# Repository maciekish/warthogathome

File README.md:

# Warthog at Home

This is a compilation of various resources to build an A-10C II cockpit for home entertainment. It is loosely based on [The Warthog Project](http://thewarthogproject.com) and frame designs by Flim on the ED forums.

This project started out as an idea for 3d-printed panels for the F-GT Lite racing chair, but as time went on it became more and more obvious that it's just too small and i would have to make way too many compromises along the way. For this reason i decided to use some of the available resources online to build a proper cockpit, but still trying to keep it as "stowable" as possible by making it modular and not mounted to the floor.

## License

This project is licensed under the MIT License except as stated otherwise in certain parts not made by me.

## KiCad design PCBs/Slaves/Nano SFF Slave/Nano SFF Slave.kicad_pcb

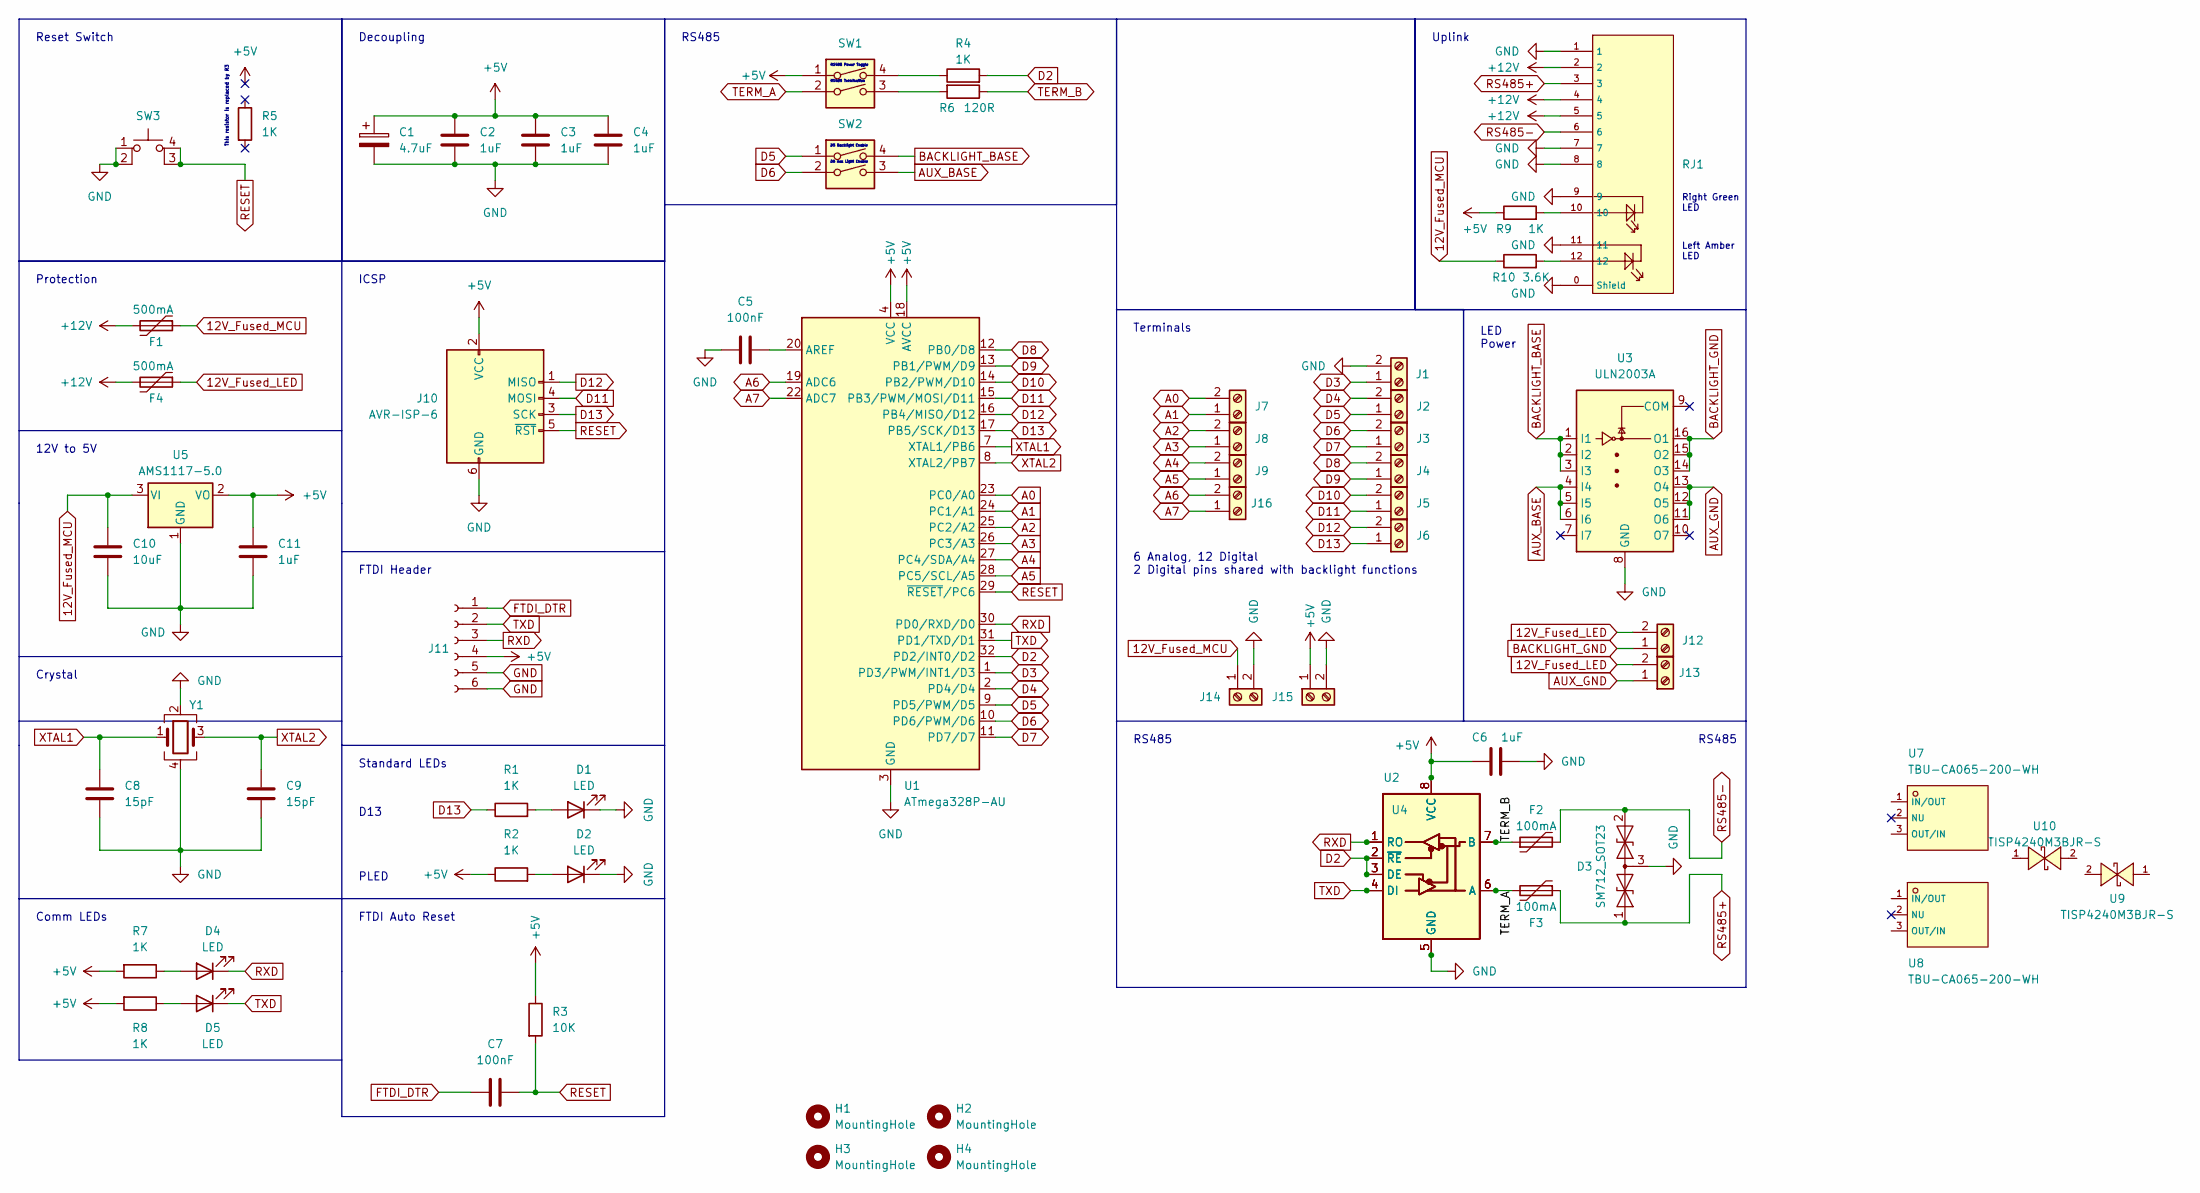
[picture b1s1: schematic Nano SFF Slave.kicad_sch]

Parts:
C1: 4.7uF; C0805; LCSC C1779
C2, C3, C4, C6, C11: 1uF; C0402; LCSC C52923
C5, C7: 100nF; C0402; LCSC C1525
C8, C9: 15pF; C0402; LCSC C1548
C10: 10uF; C0402; LCSC C15525
D1, D2, D4, D5: LED; LED_0603_1608Metric; LCSC C72041
D3: SM712_SOT23; SOT-23; LCSC C558433
F1, F4: 500mA; Fuse_1206_3216Metric; LCSC C369159
F2, F3: 100mA; Fuse_0603_1608Metric; LCSC C207238
H1, H2, H3, H4: MountingHole; MountingHole_3.2mm_M3
J1, J2, J3, J4, J5, J6, J7, J8, J9, J12, J13, J14, J15, J16: Screw_Terminal_01x02; CONN-TH_XY308-2.54-2P; LCSC C557685
J10: AVR-ISP-6; PinHeader_2x03_P2.54mm_Vertical; LCSC C492420
J11: Conn_01x06_Female; PinSocket_1x06_P2.54mm_Vertical; LCSC C40877
R1, R2, R4, R7, R8, R9: 1K; R_0402_1005Metric; LCSC C11702
R3: 10K; R_0805_2012Metric; LCSC C17414
R5: 1K; R_0805_2012Metric; LCSC C17513
R6: 120R; R_0805_2012Metric; LCSC C17437
R10: 3.6K; R_0603_1608Metric; LCSC C22980
RJ1: RJ45-B-1*1; RJ45-TH_B-1-1; LCSC C138392
SW1, SW2: SW_DIP_x02; SW-SMD_DSHP02TSGER; LCSC C367376
SW3: SW_MEC_5E; SW-SMD_4P-L5.1-W5.1-P3.70-LS6.5-TL-2; LCSC C318884
U1: ATmega328P-AU; TQFP-32_7x7mm_P0.8mm; LCSC C14877
U2: MAX487ESA+T; SOIC-8_L5.0-W4.0-P1.27-LS6.0-BL; LCSC C9953
U3: ULN2003A; SOP-16_L10.0-W3.9-P1.27-LS6.0-BL; LCSC C7512
U4: MAX487CPA+; DIP-8_W7.62mm
U5: AMS1117-5.0; SOT-223-3_TabPin2; LCSC C6187
U7, U8: TBU-CA065-200-WH; DIO-SMD_3P-L6.5-W4.0-BI; LCSC C913221
U9, U10: TISP4240M3BJR-S; DO-214AA_L4.4-W3.6-LS5.3-BI; LCSC C840526
Y1: Crystal_GND24; Crystal_SMD_3225-4Pin_3.2x2.5mm; LCSC C13738

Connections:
12V_Fused_LED: F4.1, J12.2, J13.2
12V_Fused_MCU: C10.1, F1.1, J14.1, R10.1, U5.3 (VI)
+5V: C1.1, C2.1, C3.1, C4.1, C6.1, C11.1, J10.2 (VCC), J11.4, J15.1, R2.1, R3.1, R7.2, R8.2, R9.1, SW1.1, U1.4 (VCC), U1.6 (VCC), U1.18 (AVCC), U2.8 (VCC), U4.8 (VCC), U5.2 (VO)
+12V: F1.2, F4.2, RJ1.2, RJ1.4, RJ1.5
A0: J7.2, U1.23 (PC0/A0)
A1: J7.1, U1.24 (PC1/A1)
A2: J8.2, U1.25 (PC2/A2)
A3: J8.1, U1.26 (PC3/A3)
A4: J9.2, U1.27 (PC4/SDA/A4)
A5: J9.1, U1.28 (PC5/SCL/A5)
A6: J16.2, U1.19 (ADC6)
A7: J16.1, U1.22 (ADC7)
AUX_BASE: SW2.3, U3.4 (I4), U3.5 (I5), U3.6 (I6)
AUX_GND: J13.1, U3.11 (O6), U3.12 (O5), U3.13 (O4)
BACKLIGHT_BASE: SW2.4, U3.1 (I1), U3.2 (I2), U3.3 (I3)
BACKLIGHT_GND: J12.1, U3.14 (O3), U3.15 (O2), U3.16 (O1)
D2: R4.2, U1.32 (PD2/INT0/D2), U2.2 (~RE), U2.3 (DE), U4.2 (~RE), U4.3 (DE)
D3: J1.1, U1.1 (PD3/PWM/INT1/D3)
D4: J2.2, U1.2 (PD4/D4)
D5: J2.1, SW2.1, U1.9 (PD5/PWM/D5)
D6: J3.2, SW2.2, U1.10 (PD6/PWM/D6)
D7: J3.1, U1.11 (PD7/D7)
D8: J4.2, U1.12 (PB0/D8)
D9: J4.1, U1.13 (PB1/PWM/D9)
D10: J5.2, U1.14 (PB2/PWM/D10)
D11: J5.1, J10.4 (MOSI), U1.15 (PB3/PWM/MOSI/D11)
D12: J6.2, J10.1 (MISO), U1.16 (PB4/MISO/D12)
D13: J6.1, J10.3 (SCK), R1.1, U1.17 (PB5/SCK/D13)
FTDI_DTR: C7.2, J11.1
GND: C1.2, C2.2, C3.2, C4.2, C5.1, C6.2, C8.1, C9.2, C10.2, C11.2, D1.1 (K), D2.1 (K), D3.3 (common), J1.2, J10.6 (GND), J11.5, J11.6, J14.2, J15.2, RJ1.0 (Shield), RJ1.1, RJ1.7, RJ1.8, RJ1.9, RJ1.11, SW3.1, SW3.2, U1.3 (GND), U1.5 (GND), U1.21 (GND), U2.5 (GND), U3.8 (GND), U4.5 (GND), U5.1 (GND), Y1.2, Y1.4
unnamed: C5.2, U1.20 (AREF)
unnamed: D1.2 (A), R1.2
unnamed: D2.2 (A), R2.2
unnamed: D4.2 (A), R7.1
unnamed: D5.2 (A), R8.1
unnamed: R4.1, SW1.4
unnamed: R6.2, SW1.3
unnamed: R9.2, RJ1.10
unnamed: R10.2, RJ1.12
RESET: C7.1, J10.5 (~RST), R3.2, SW3.3 (K), SW3.4 (A), U1.29 (~RESET/PC6)
RS485+: D3.1 (A1), F3.1, RJ1.3
RS485-: D3.2 (A2), F2.2, RJ1.6
RXD: D4.1 (K), J11.3, U1.30 (PD0/RXD/D0), U2.1 (RO), U4.1 (RO)
TERM_A: F3.2, SW1.2, U2.6 (A), U4.6 (A)
TERM_B: F2.1, R6.1, U2.7 (B), U4.7 (B)
TXD: D5.1 (K), J11.2, U1.31 (PD1/TXD/D1), U2.4 (DI), U4.4 (DI)
XTAL1: C8.2, U1.7 (XTAL1/PB6), Y1.1
XTAL2: C9.1, U1.8 (XTAL2/PB7), Y1.3

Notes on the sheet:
RS485
Comm LEDs
Decoupling
Left Amber LED
D13
12V to 5V
Uplink
D5 Backlight Enable
RS485 Power Toggle
Protection
6 Analog, 12 Digital 2 Digital pins shared with backlight functions
Terminals
RS485 Termination
PLED
FTDI Header
D6 Aux Light Enable
Standard LEDs
LED Power
Right Green LED
FTDI Auto Reset
Reset Switch
Crystal
ICSP
This resistor is replaced by R3

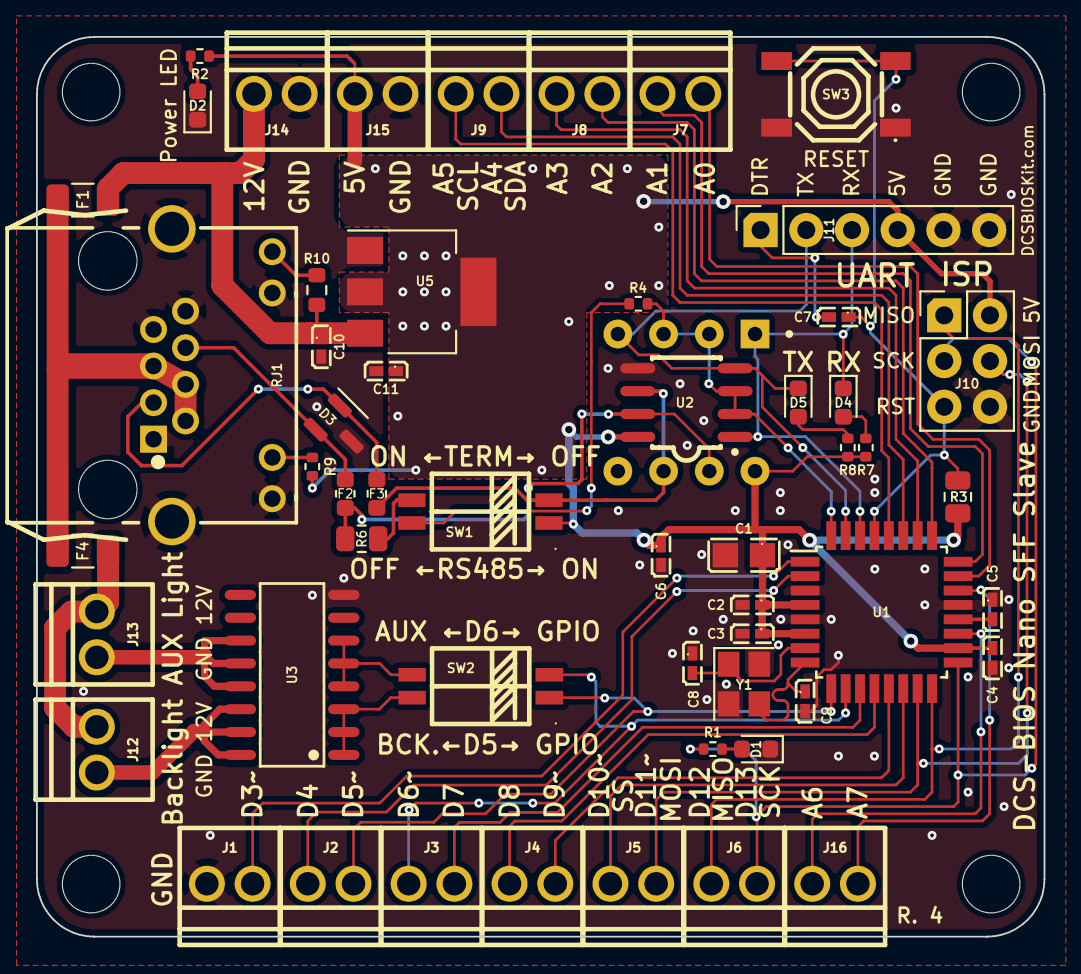
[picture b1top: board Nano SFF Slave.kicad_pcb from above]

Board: 2 copper layers, 56.0 x 50.0 mm, 59 parts (0 on the bottom side), 48 nets.

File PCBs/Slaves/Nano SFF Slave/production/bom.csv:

Designator,Footprint,Quantity,Value,LCSC Part #
J3,CONN-TH_XY308-2.54-2P,1,Screw_Terminal_01x02,C557685
R4,R_0402_1005Metric,1,1K,C11702
J10,PinHeader_2x03_P2.54mm_Vertical,1,AVR-ISP-6,C492420
J5,CONN-TH_XY308-2.54-2P,1,Screw_Terminal_01x02,C557685
F4,Fuse_1206_3216Metric,1,500mA,C369159
H4,MountingHole_3.2mm_M3,1,MountingHole,
R2,R_0402_1005Metric,1,1K,C11702
C6,C0402,1,1uF,C52923
U5,SOT-223-3_TabPin2,1,AMS1117-5.0,C6187
F1,Fuse_1206_3216Metric,1,500mA,C369159
H3,MountingHole_3.2mm_M3,1,MountingHole,
R7,R_0402_1005Metric,1,1K,C11702
D5,LED_0603_1608Metric,1,LED,C72041
C3,C0402,1,1uF,C52923
J15,CONN-TH_XY308-2.54-2P,1,Screw_Terminal_01x02,C557685
C1,C0805,1,4.7uF,C1779
C5,C0402,1,100nF,C1525
U3,SOP-16_L10.0-W3.9-P1.27-LS6.0-BL,1,ULN2003A,C7512
C11,C0402,1,1uF,C52923
C2,C0402,1,1uF,C52923
U2,SOIC-8_L5.0-W4.0-P1.27-LS6.0-BL,1,MAX487ESA+T,C9953
J14,CONN-TH_XY308-2.54-2P,1,Screw_Terminal_01x02,C557685
D2,LED_0603_1608Metric,1,LED,C72041
R8,R_0402_1005Metric,1,1K,C11702
H1,MountingHole_3.2mm_M3,1,MountingHole,
J1,CONN-TH_XY308-2.54-2P,1,Screw_Terminal_01x02,C557685
J6,CONN-TH_XY308-2.54-2P,1,Screw_Terminal_01x02,C557685
R6,R_0805_2012Metric,1,120R,C17437
J9,CONN-TH_XY308-2.54-2P,1,Screw_Terminal_01x02,C557685
J2,CONN-TH_XY308-2.54-2P,1,Screw_Terminal_01x02,C557685
SW3,SW-SMD_4P-L5.1-W5.1-P3.70-LS6.5-TL-2,1,SW_MEC_5E,C318884
C10,C0402,1,10uF,C15525
D3,SOT-23,1,SM712_SOT23,C558433
SW2,SW-SMD_DSHP02TSGER,1,SW_DIP_x02,C367376
F3,Fuse_0603_1608Metric,1,100mA,C207238
C4,C0402,1,1uF,C52923
J4,CONN-TH_XY308-2.54-2P,1,Screw_Terminal_01x02,C557685
RJ1,RJ45-TH_B-1-1,1,RJ45-B-1*1,C138392
C7,C0402,1,100nF,C1525
R9,R_0402_1005Metric,1,1K,C11702
R1,R_0402_1005Metric,1,1K,C11702
C9,C0402,1,15pF,C1548
SW1,SW-SMD_DSHP02TSGER,1,SW_DIP_x02,C367376
J13,CONN-TH_XY308-2.54-2P,1,Screw_Terminal_01x02,C557685
J16,CONN-TH_XY308-2.54-2P,1,Screw_Terminal_01x02,C557685
J12,CONN-TH_XY308-2.54-2P,1,Screw_Terminal_01x02,C557685
Y1,Crystal_SMD_3225-4Pin_3.2x2.5mm,1,Crystal_GND24,C13738
U1,TQFP-32_7x7mm_P0.8mm,1,ATmega328P-AU,C14877
R10,R_0603_1608Metric,1,3.6K,C22980
J11,PinSocket_1x06_P2.54mm_Vertical,1,Conn_01x06_Female,C40877
H2,MountingHole_3.2mm_M3,1,MountingHole,
R3,R_0805_2012Metric,1,10K,C17414
D4,LED_0603_1608Metric,1,LED,C72041
J8,CONN-TH_XY308-2.54-2P,1,Screw_Terminal_01x02,C557685
F2,Fuse_0603_1608Metric,1,100mA,C207238
C8,C0402,1,15pF,C1548
J7,CONN-TH_XY308-2.54-2P,1,Screw_Terminal_01x02,C557685
D1,LED_0603_1608Metric,1,LED,C72041

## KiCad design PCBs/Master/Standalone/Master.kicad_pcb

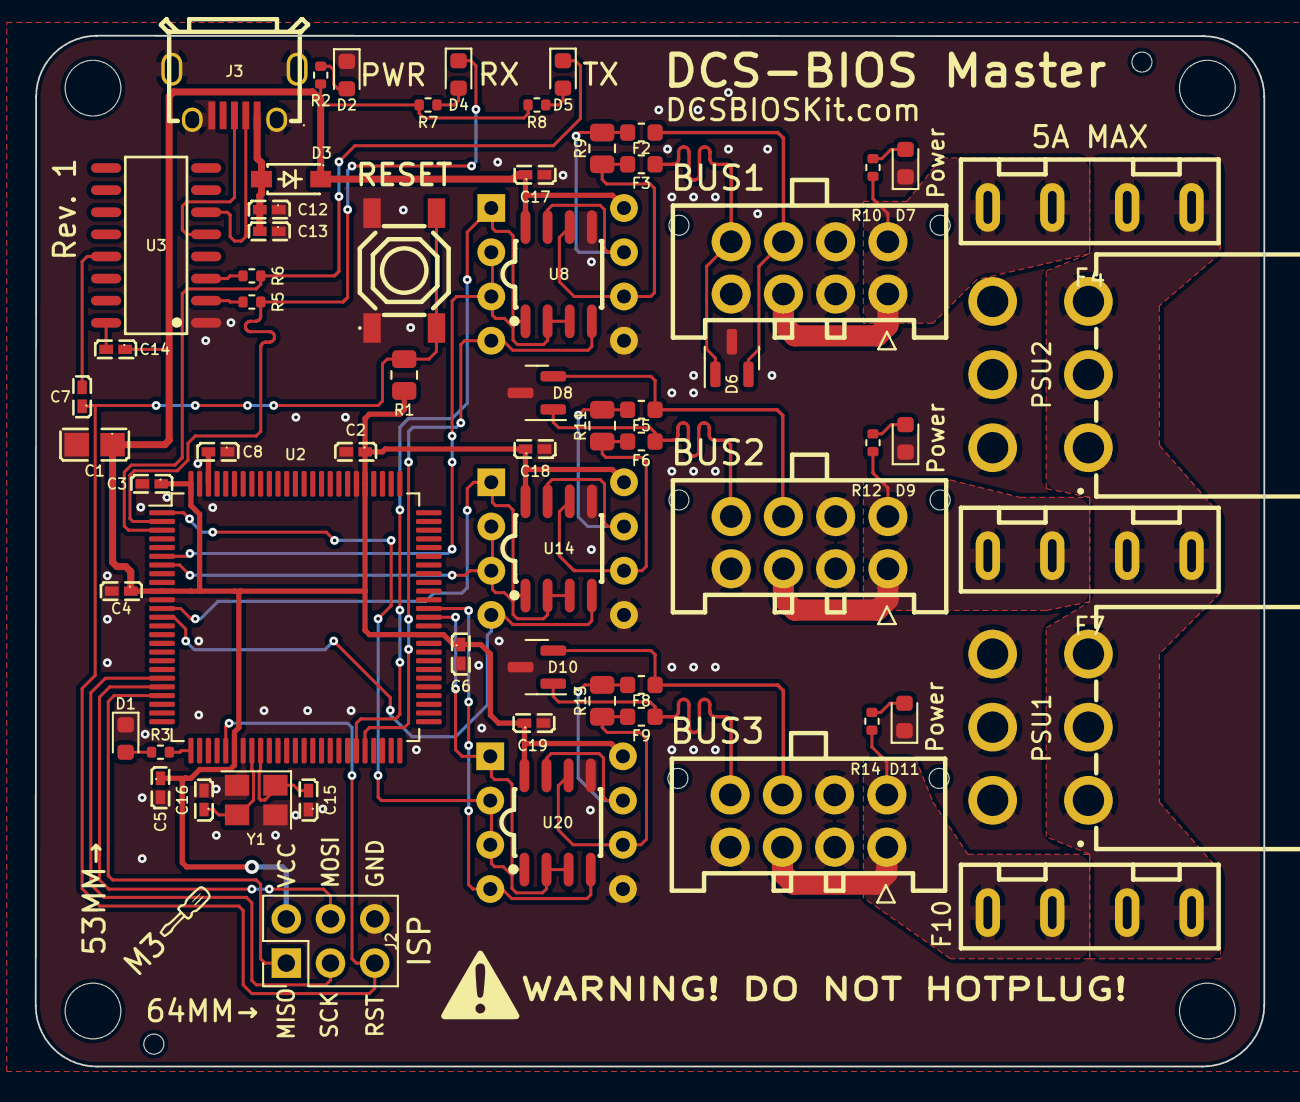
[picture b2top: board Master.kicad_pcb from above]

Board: 2 copper layers, 70.6 x 59.2 mm, 71 parts (1 on the bottom side), 51 nets.

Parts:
BUS1, BUS2, BUS3: Conn_02x04_Top_Bottom; Molex Micro-Fit 3.0 43045-0812
C1: 4.7uF; C0805
C2, C3, C4, C5, C6, C14, C17, C18, C19: 1uF; C0402
C7, C8, C12: 100nF; C0402
C13: 10uF; C0402
C15, C16: 15pF; C0402
D1, D2, D4, D5: LED; LED_0603_1608Metric
D3: DIODE; SOD-123_L2.7-W1.6-LS3.7-RD-1
D6, D8, D10: SM712_SOT23; SOT-23
D7, D9, D11: BLUE; LED_0603_1608Metric
F2, F3, F5, F6, F8, F9: 100mA; Fuse_0603_1608Metric
F4, F7, F10: 5A; FUSE-TH_XF-506P
Ge: LOGO
H1, H2, H3, H4: MountingHole; MountingHole_3.2mm_M3
J2: AVR-ISP-6; PinHeader_2x03_P2.54mm_Vertical
J3: USB_B_Micro; MICRO-USB-SMD_U254-051T-4BHJ25-F2S
PSU1, PSU2: Conn_02x03_Odd_Even; CONN-TH_HAA420A-6AW-C2845788
R1: 10K; R_0805_2012Metric
R2, R3, R5, R6, R7, R8: 1K; R_0402_1005Metric
R9, R11, R13: 120R; R_0805_2012Metric
R10, R12, R14: 3.3K; R_0402_1005Metric
SW1: SW_MEC_5E; SW-SMD_4P-L5.1-W5.1-P3.70-LS6.5-TL-2
U2: ATmega2560-16A; TQFP-100_14x14mm_P0.5mm
U3: CH340C; SOP-16_L10.0-W3.9-P1.27-LS6.0-BL
U7, U13, U19: MAX487ESA+T; DIP-8_W7.62mm
U8, U14, U20: MAX487ESA+T; SOIC-8_L5.0-W4.0-P1.27-LS6.0-BL
Y1: Crystal_GND24; Crystal_SMD_3225-4Pin_3.2x2.5mm

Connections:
+5V: C1.1, C2.1, C3.1, C4.1, C5.1, C6.1, C14.1, C17.1, C18.1, C19.1, D3.2 (A), J2.2 (VCC), R1.1, R2.1, R7.2, R8.2, U2.10 (VCC), U2.31 (VCC), U2.61 (VCC), U2.80 (VCC), U2.100 (AVCC), U7.8 (VCC), U8.8 (VCC), U13.8 (VCC), U14.8 (VCC), U19.8 (VCC), U20.8 (VCC)
+12V: F4.1, F7.1, F10.1, PSU1.1, PSU1.3, PSU1.5, PSU2.1, PSU2.3, PSU2.5
D2: U2.6 (PE4/~D2), U7.2 (~RE), U7.3 (DE), U8.2 (~RE), U8.3 (DE)
D3: U2.7 (PE5/~D3), U13.2 (~RE), U13.3 (DE), U14.2 (~RE), U14.3 (DE)
D4: U2.1 (PG5/~D4), U19.2 (~RE), U19.3 (DE), U20.2 (~RE), U20.3 (DE)
D13: R3.1, U2.26 (PB7/~D13)
D14: U2.64 (PJ1/TXD3/D14), U19.4 (DI), U20.4 (DI)
D15: U2.63 (PJ0/RXD3/D15), U19.1 (RO), U20.1 (RO)
D16: U2.13 (PH1/TXD2/D16), U13.4 (DI), U14.4 (DI)
D17: U2.12 (PH0/RXD2/D17), U13.1 (RO), U14.1 (RO)
D18: U2.46 (PD3/TXD1/D18), U7.4 (DI), U8.4 (DI)
D19: U2.45 (PD2/RXD1/D19), U7.1 (RO), U8.1 (RO)
D50: J2.1 (MISO), U2.22 (PB3/MISO/D50)
D51: J2.4 (MOSI), U2.21 (PB2/MOSI/D51)
D52: J2.3 (SCK), U2.20 (PB1/SCK/D52)
D+: J3.3 (D+), U3.5 (UD+)
D-: J3.2 (D-), U3.6 (UD-)
FTDI_DTR: C7.2, U3.13 (~DTR)
GND: BUS1.2, BUS1.4, BUS1.6, BUS2.2, BUS2.4, BUS2.6, BUS3.2, BUS3.4, BUS3.6, C1.2, C2.2, C3.2, C4.2, C5.2, C6.2, C8.1, C12.1, C13.1, C15.1, C16.2, C17.2, C18.2, C19.2, D1.1 (K), D2.1 (K), D6.3 (common), D7.1 (K), D8.3 (common), D9.1 (K), D10.3 (common), D11.1 (K), J2.6 (GND), J3.5 (GND), J3.6 (Shield), PSU1.2, PSU1.4, PSU1.6, PSU2.2, PSU2.4, PSU2.6, SW1.1, SW1.2, U2.11 (GND), U2.32 (GND), U2.62 (GND), U2.81 (GND), U2.99 (GND), U3.1 (GND), U7.5 (GND), U8.5 (GND), U13.5 (GND), U14.5 (GND), U19.5 (GND), U20.5 (GND), Y1.2, Y1.4
unnamed: BUS1.1, BUS1.3, BUS1.5, F4.2, R10.2
unnamed: BUS2.1, BUS2.3, BUS2.5, F7.2, R12.2
unnamed: BUS3.1, BUS3.3, BUS3.5, F10.2, R14.2
unnamed: C8.2, U2.98 (AREF)
unnamed: C12.2, C13.2, D3.1 (K), J3.1 (VBUS)
unnamed: C14.2, U3.16 (VCC)
unnamed: D1.2 (A), R3.2
unnamed: D2.2 (A), R2.2
unnamed: D4.2 (A), R7.1
unnamed: D5.2 (A), R8.1
unnamed: D7.2 (A), R10.1
unnamed: D9.2 (A), R12.1
unnamed: D11.2 (A), R14.1
unnamed: F2.1, R9.1, U7.7 (B), U8.7 (B)
unnamed: F3.2, R9.2, U7.6 (A), U8.6 (A)
unnamed: F5.1, R11.1, U13.7 (B), U14.7 (B)
unnamed: F6.2, R11.2, U13.6 (A), U14.6 (A)
unnamed: F8.1, R13.1, U19.7 (B), U20.7 (B)
unnamed: F9.2, R13.2, U19.6 (A), U20.6 (A)
unnamed: R5.1, U3.2 (TXD)
unnamed: R6.1, U3.3 (RXD)
RESET: C7.1, J2.5 (~RST), R1.2, SW1.3 (K), SW1.4 (A), U2.30 (~RESET)
RS485-1+: BUS1.8, D6.1 (A1), F3.1
RS485-1-: BUS1.7, D6.2 (A2), F2.2
RS485-2+: BUS2.8, D8.1 (A1), F6.1
RS485-2-: BUS2.7, D8.2 (A2), F5.2
RS485-3+: BUS3.8, D10.1 (A1), F9.1
RS485-3-: BUS3.7, D10.2 (A2), F8.2
USB_RXD: D5.1 (K), R6.2, U2.3 (PE1/TXD0/~D1)
USB_TXD: D4.1 (K), R5.2, U2.2 (PE0/RXD0/~D0)
XTAL1: C15.2, U2.34 (XTAL1), Y1.1
XTAL2: C16.1, U2.33 (XTAL2), Y1.3

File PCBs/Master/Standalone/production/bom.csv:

Designator,Footprint,Quantity,Value,LCSC Part #
F9,Fuse_0603_1608Metric,1,100mA,C207238
R12,R_0402_1005Metric,1,3.3K,C25890
U8,SOIC-8_L5.0-W4.0-P1.27-LS6.0-BL,1,MAX487ESA+T,C9953
D2,LED_0603_1608Metric,1,LED,C72041
F2,Fuse_0603_1608Metric,1,100mA,C207238
U19,DIP-8_W7.62mm,1,MAX487ESA+T,C9953
D6,SOT-23,1,SM712_SOT23,C558433
R6,R_0402_1005Metric,1,1K,C11702
D9,LED_0603_1608Metric,1,BLUE,C72041
D7,LED_0603_1608Metric,1,BLUE,C72041
PSU1,CONN-TH_HAA420A-6AW-C2845788,1,Conn_02x03_Odd_Even,C2845788
D4,LED_0603_1608Metric,1,LED,C72041
C16,C0402,1,15pF,C1548
U3,SOP-16_L10.0-W3.9-P1.27-LS6.0-BL,1,CH340C,C84681
R3,R_0402_1005Metric,1,1K,C11702
U14,SOIC-8_L5.0-W4.0-P1.27-LS6.0-BL,1,MAX487ESA+T,C9953
BUS1,Molex Micro-Fit 3.0 43045-0812,1,Conn_02x04_Top_Bottom,C277661
D8,SOT-23,1,SM712_SOT23,C558433
C14,C0402,1,1uF,C52923
F6,Fuse_0603_1608Metric,1,100mA,C207238
C2,C0402,1,1uF,C52923
R1,R_0805_2012Metric,1,10K,C17414
F8,Fuse_0603_1608Metric,1,100mA,C207238
D3,SOD-123_L2.7-W1.6-LS3.7-RD-1,1,DIODE,C8598
Y1,Crystal_SMD_3225-4Pin_3.2x2.5mm,1,Crystal_GND24,C13738
C6,C0402,1,1uF,C52923
U2,TQFP-100_14x14mm_P0.5mm,1,ATmega2560-16A,C22460
SW1,SW-SMD_4P-L5.1-W5.1-P3.70-LS6.5-TL-2,1,SW_MEC_5E,C318884
PSU2,CONN-TH_HAA420A-6AW-C2845788,1,Conn_02x03_Odd_Even,C2845788
BUS3,Molex Micro-Fit 3.0 43045-0812,1,Conn_02x04_Top_Bottom,C277661
F7,FUSE-TH_XF-506P,1,5A,C492610
F5,Fuse_0603_1608Metric,1,100mA,C207238
R10,R_0402_1005Metric,1,3.3K,C25890
U20,SOIC-8_L5.0-W4.0-P1.27-LS6.0-BL,1,MAX487ESA+T,C9953
C12,C0402,1,100nF,C1525
C8,C0402,1,100nF,C1525
R5,R_0402_1005Metric,1,1K,C11702
D1,LED_0603_1608Metric,1,LED,C72041
C1,C0805,1,4.7uF,C1779
R7,R_0402_1005Metric,1,1K,C11702
C17,C0402,1,1uF,C52923
C5,C0402,1,1uF,C52923
C13,C0402,1,10uF,C15525
D5,LED_0603_1608Metric,1,LED,C72041
C15,C0402,1,15pF,C1548
D11,LED_0603_1608Metric,1,BLUE,C72041
D10,SOT-23,1,SM712_SOT23,C558433
F4,FUSE-TH_XF-506P,1,5A,C492610
C4,C0402,1,1uF,C52923
U13,DIP-8_W7.62mm,1,MAX487ESA+T,C9953
R9,R_0805_2012Metric,1,120R,C17437
C19,C0402,1,1uF,C52923
R11,R_0805_2012Metric,1,120R,C17437
BUS2,Molex Micro-Fit 3.0 43045-0812,1,Conn_02x04_Top_Bottom,C277661
C18,C0402,1,1uF,C52923
R2,R_0402_1005Metric,1,1K,C11702
J2,PinHeader_2x03_P2.54mm_Vertical,1,AVR-ISP-6,C492420
R14,R_0402_1005Metric,1,3.3K,C25890
R13,R_0805_2012Metric,1,120R,C17437
R8,R_0402_1005Metric,1,1K,C11702
C3,C0402,1,1uF,C52923
C7,C0402,1,100nF,C1525
U7,DIP-8_W7.62mm,1,MAX487ESA+T,C9953
F3,Fuse_0603_1608Metric,1,100mA,C207238
F10,FUSE-TH_XF-506P,1,5A,C492610
J3,MICRO-USB-SMD_U254-051T-4BHJ25-F2S,1,USB_B_Micro,C381143

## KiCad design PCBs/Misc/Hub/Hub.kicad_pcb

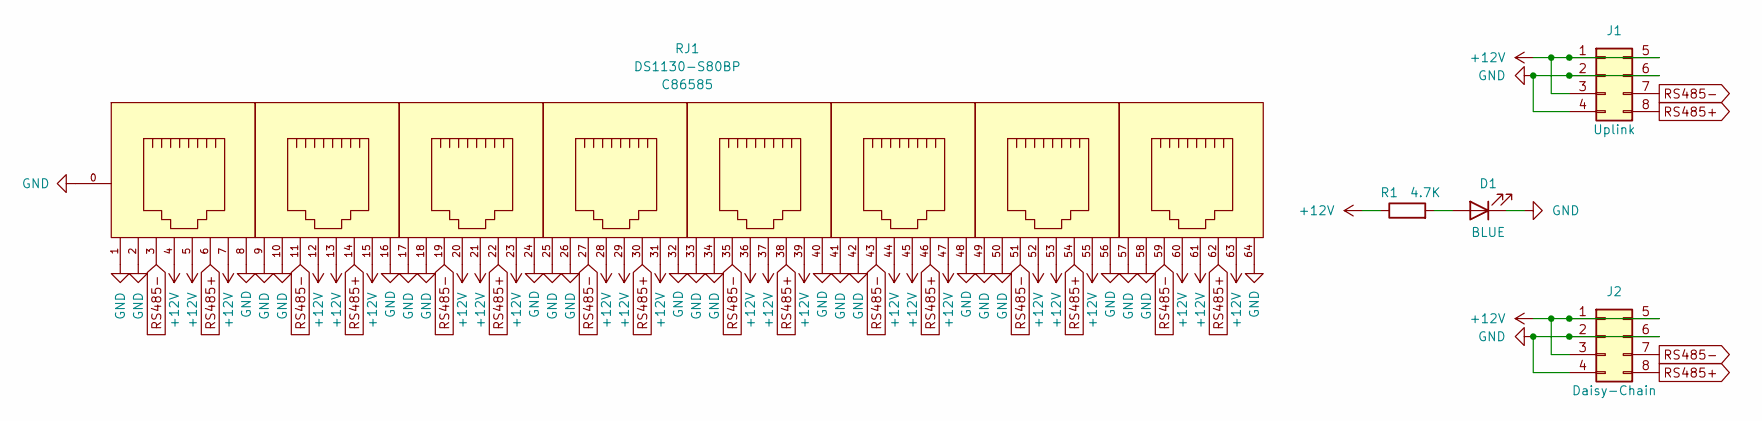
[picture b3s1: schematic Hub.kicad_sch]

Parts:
D1: BLUE; LED_0603_1608Metric; LCSC C72041
J1, J2: Conn_02x04_Top_Bottom; Molex Micro-Fit 3.0 43045-0800; LCSC C122422
R1: 4.7K; R_0603_1608Metric; LCSC C23162
RJ1: DS1130-S80BP; RJ45-TH_DS1130-S80BP; LCSC C86585

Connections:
+12V: J1.1, J1.3, J1.5, J2.1, J2.3, J2.5, R1.1, RJ1.4, RJ1.5, RJ1.7, RJ1.12, RJ1.13, RJ1.15, RJ1.20, RJ1.21, RJ1.23, RJ1.28, RJ1.29, RJ1.31, RJ1.36, RJ1.37, RJ1.39, RJ1.44, RJ1.45, RJ1.47, RJ1.52, RJ1.53, RJ1.55, RJ1.60, RJ1.61, RJ1.63
GND: D1.1 (K), J1.2, J1.4, J1.6, J2.2, J2.4, J2.6, RJ1.0, RJ1.1, RJ1.2, RJ1.8, RJ1.9, RJ1.10, RJ1.16, RJ1.17, RJ1.18, RJ1.24, RJ1.25, RJ1.26, RJ1.32, RJ1.33, RJ1.34, RJ1.40, RJ1.41, RJ1.42, RJ1.48, RJ1.49, RJ1.50, RJ1.56, RJ1.57, RJ1.58, RJ1.64
unnamed: D1.2 (A), R1.2
RS485+: J1.8, J2.8, RJ1.6, RJ1.14, RJ1.22, RJ1.30, RJ1.38, RJ1.46, RJ1.54, RJ1.62
RS485-: J1.7, J2.7, RJ1.3, RJ1.11, RJ1.19, RJ1.27, RJ1.35, RJ1.43, RJ1.51, RJ1.59

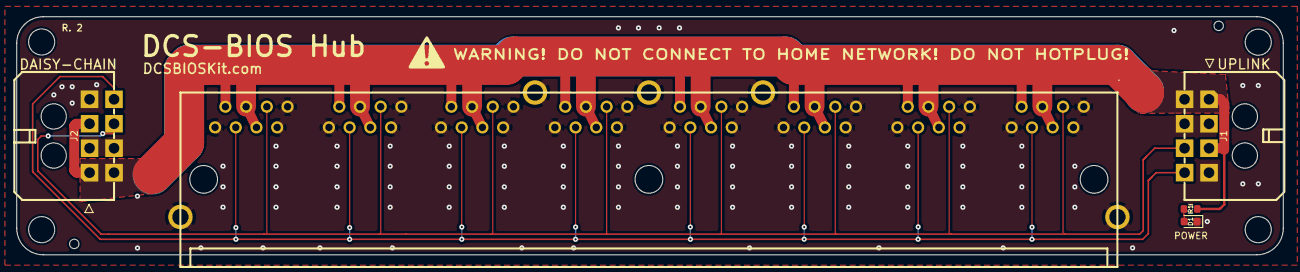
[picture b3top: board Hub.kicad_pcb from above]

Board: 2 copper layers, 155.4 x 29.2 mm, 9 parts (0 on the bottom side), 5 nets.

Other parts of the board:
HOLE-3, HOLE-3#2, HOLE-4, HOLE-4#2: MountingHole_3.2mm_M3

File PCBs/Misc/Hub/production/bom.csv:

Designator,Footprint,Quantity,Value,LCSC Part #
J2,Molex Micro-Fit 3.0 43045-0800,1,Conn_02x04_Top_Bottom,C122422
RJ1,RJ45-TH_DS1130-S80BP,1,DS1130-S80BP,C86585
D1,LED_0603_1608Metric,1,BLUE,C72041
R1,R_0603_1608Metric,1,4.7K,C23162
J1,Molex Micro-Fit 3.0 43045-0800,1,Conn_02x04_Top_Bottom,C122422

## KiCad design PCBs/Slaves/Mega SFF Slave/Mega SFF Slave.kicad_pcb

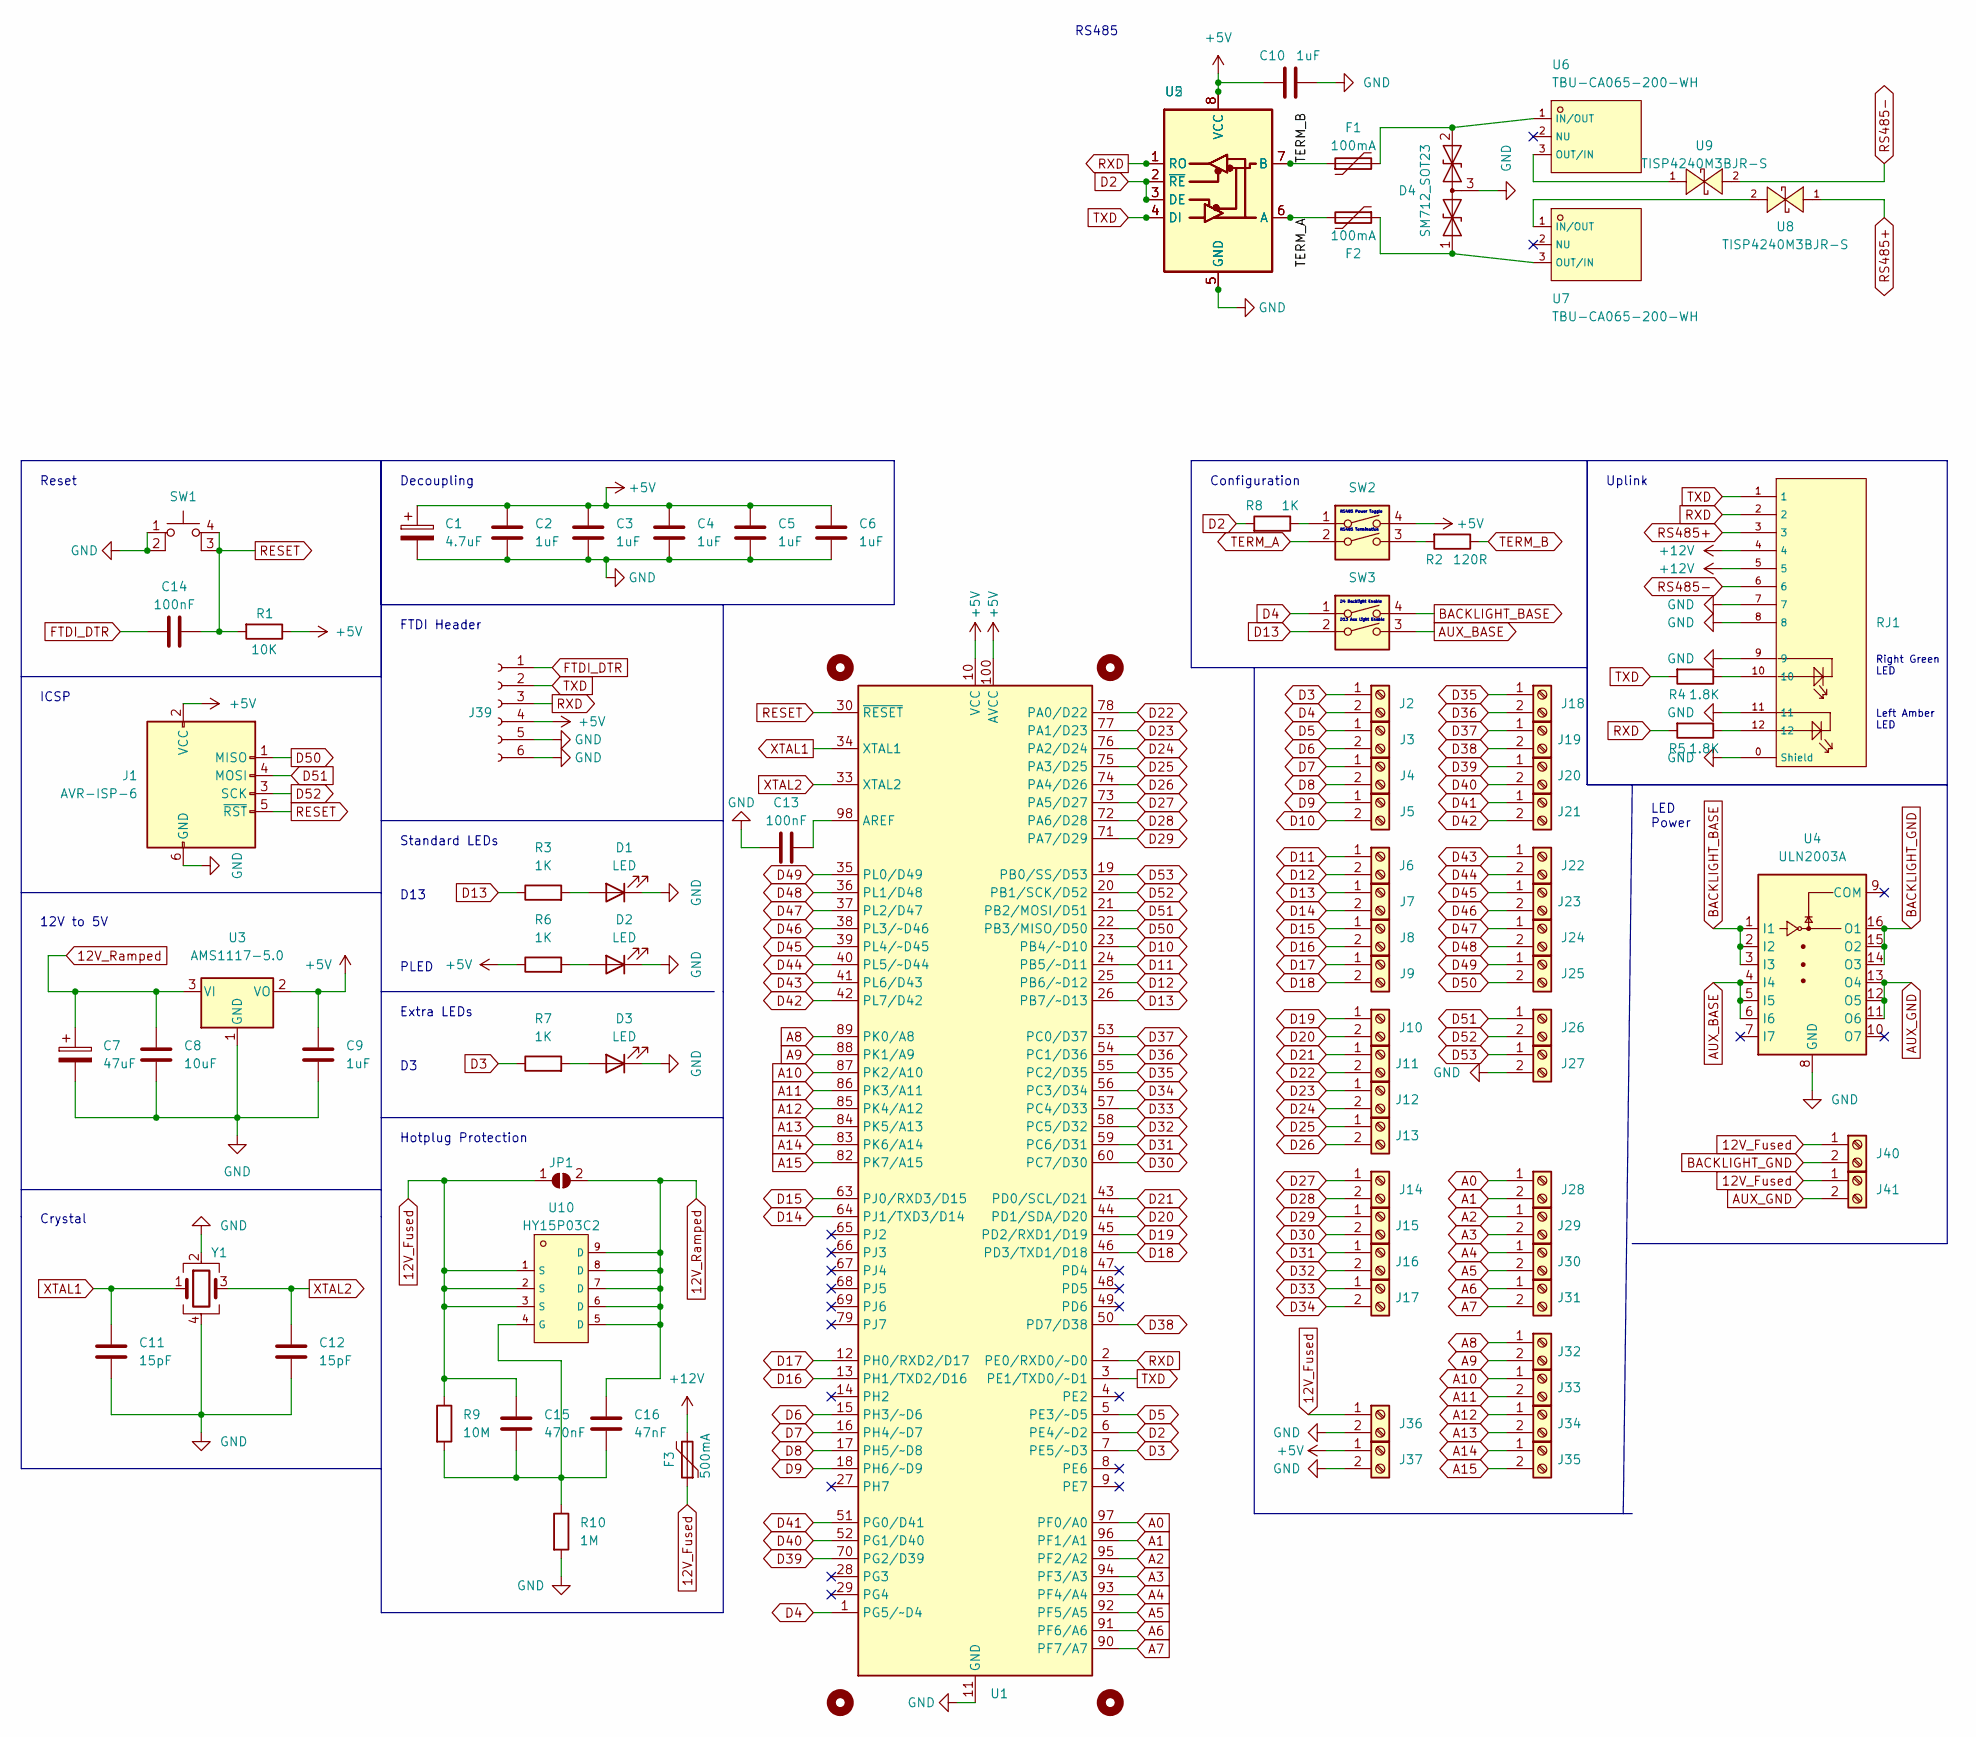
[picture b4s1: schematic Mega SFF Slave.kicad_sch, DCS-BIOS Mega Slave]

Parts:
C1: 4.7uF; C0805; LCSC C1779
C2, C3, C4, C5, C6, C9, C10: 1uF; C0402; LCSC C52923
C7: 47uF; CP_Elec_5x5.4; LCSC C96178
C8: 10uF; C0402; LCSC C15525
C11, C12: 15pF; C0402; LCSC C1548
C13, C14: 100nF; C0402; LCSC C1525
C15: 470nF; C_0603_1608Metric; LCSC C1623
C16: 47nF; C_0603_1608Metric; LCSC C1622
D1, D2, D3: LED; LED_0603_1608Metric; LCSC C72041
D4: SM712_SOT23; SOT-23; LCSC C558433
F1, F2: 100mA; Fuse_0603_1608Metric; LCSC C207238
F3: 500mA; Fuse_1206_3216Metric; LCSC C369159
H1, H2, H3, H4: MountingHole; MountingHole_3.2mm_M3
J1: AVR-ISP-6; PinHeader_2x03_P2.54mm_Vertical; LCSC C492420
J2, J3, J4, J5, J6, J7, J8, J9, J10, J11, J12, J13, J14, J15, J16, J17, J18, J19, J20, J21, J22, J23, J24, J25, J26, J27, J28, J29, J30, J31, J32, J33, J34, J35, J36, J37, J40, J41: Screw_Terminal_01x02; CONN-TH_XY308-2.54-2P; LCSC C557685
J39: Conn_01x06_Female; PinSocket_1x06_P2.54mm_Vertical; LCSC C40877
JP1: Solder; SolderJumper-2_P1.3mm_Open_RoundedPad1.0x1.5mm
R1: 10K; R_0805_2012Metric; LCSC C17414
R2: 120R; R_0805_2012Metric; LCSC C17437
R3, R6, R7, R8: 1K; R_0805_2012Metric; LCSC C17513
R4, R5: 1.8K; R_0805_2012Metric; LCSC C17398
R9: 10M; R_0603_1608Metric; LCSC C7250
R10: 1M; R_0603_1608Metric; LCSC C22935
RJ1: RJ45-B-1*1; RJ45-TH_B-1-1; LCSC C138392
SW1: SW_MEC_5E; SW-SMD_4P-L5.1-W5.1-P3.70-LS6.5-TL-2; LCSC C318884
SW2, SW3: SW_DIP_x02; SW-SMD_DSHP02TSGER; LCSC C367376
U1: ATmega2560-16A; TQFP-100_14x14mm_P0.5mm; LCSC C22460
U2: MAX487ESA+T; SOIC-8_L5.0-W4.0-P1.27-LS6.0-BL; LCSC C9953
U3: AMS1117-5.0; SOT-223-3_TabPin2; LCSC C6187
U4: ULN2003A; SOP-16_L10.0-W3.9-P1.27-LS6.0-BL; LCSC C7512
U5: MAX487ESA+T; DIP-8_W7.62mm; LCSC C9953
U6, U7: TBU-CA065-200-WH; DIO-SMD_3P-L6.5-W4.0-BI; LCSC C913221
U8, U9: TISP4240M3BJR-S; DO-214AA_L4.4-W3.6-LS5.3-BI; LCSC C840526
U10: HY15P03C2; DFN-8_L5.9-W5.2-P1.27-LS6.2-BL; LCSC C123687
Y1: Crystal_GND24; Crystal_SMD_3225-4Pin_3.2x2.5mm; LCSC C13738

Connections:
12V_Fused: C15.1, F3.1, J36.1, J40.1, J41.1, JP1.1 (A), R9.1, U10.1 (S), U10.2 (S), U10.3 (S)
12V_Ramped: C7.1, C8.1, C16.1, JP1.2 (B), U3.3 (VI), U10.5 (D), U10.6 (D), U10.7 (D), U10.8 (D), U10.9 (D)
+5V: C1.1, C2.1, C3.1, C4.1, C5.1, C6.1, C9.1, C10.1, J1.2 (VCC), J37.1, J39.4, R1.1, R6.1, SW2.4, U1.10 (VCC), U1.31 (VCC), U1.61 (VCC), U1.80 (VCC), U1.100 (AVCC), U2.8 (VCC), U3.2 (VO), U5.8 (VCC)
+12V: F3.2, RJ1.4, RJ1.5
A0: J28.1, U1.97 (PF0/A0)
A1: J28.2, U1.96 (PF1/A1)
A2: J29.1, U1.95 (PF2/A2)
A3: J29.2, U1.94 (PF3/A3)
A4: J30.1, U1.93 (PF4/A4)
A5: J30.2, U1.92 (PF5/A5)
A6: J31.1, U1.91 (PF6/A6)
A7: J31.2, U1.90 (PF7/A7)
A8: J32.1, U1.89 (PK0/A8)
A9: J32.2, U1.88 (PK1/A9)
A10: J33.1, U1.87 (PK2/A10)
A11: J33.2, U1.86 (PK3/A11)
A12: J34.1, U1.85 (PK4/A12)
A13: J34.2, U1.84 (PK5/A13)
A14: J35.1, U1.83 (PK6/A14)
A15: J35.2, U1.82 (PK7/A15)
AUX_BASE: SW3.3, U4.4 (I4), U4.5 (I5), U4.6 (I6)
AUX_GND: J41.2, U4.11 (O6), U4.12 (O5), U4.13 (O4)
BACKLIGHT_BASE: SW3.4, U4.1 (I1), U4.2 (I2), U4.3 (I3)
BACKLIGHT_GND: J40.2, U4.14 (O3), U4.15 (O2), U4.16 (O1)
D2: R8.2, U1.6 (PE4/~D2), U2.2 (~RE), U2.3 (DE), U5.2 (~RE), U5.3 (DE)
D3: J2.1, R7.1, U1.7 (PE5/~D3)
D4: J2.2, SW3.1, U1.1 (PG5/~D4)
D5: J3.1, U1.5 (PE3/~D5)
D6: J3.2, U1.15 (PH3/~D6)
D7: J4.1, U1.16 (PH4/~D7)
D8: J4.2, U1.17 (PH5/~D8)
D9: J5.1, U1.18 (PH6/~D9)
D10: J5.2, U1.23 (PB4/~D10)
D11: J6.1, U1.24 (PB5/~D11)
D12: J6.2, U1.25 (PB6/~D12)
D13: J7.1, R3.1, SW3.2, U1.26 (PB7/~D13)
D14: J7.2, U1.64 (PJ1/TXD3/D14)
D15: J8.1, U1.63 (PJ0/RXD3/D15)
D16: J8.2, U1.13 (PH1/TXD2/D16)
D17: J9.1, U1.12 (PH0/RXD2/D17)
D18: J9.2, U1.46 (PD3/TXD1/D18)
D19: J10.1, U1.45 (PD2/RXD1/D19)
D20: J10.2, U1.44 (PD1/SDA/D20)
D21: J11.1, U1.43 (PD0/SCL/D21)
D22: J11.2, U1.78 (PA0/D22)
D23: J12.1, U1.77 (PA1/D23)
D24: J12.2, U1.76 (PA2/D24)
D25: J13.1, U1.75 (PA3/D25)
D26: J13.2, U1.74 (PA4/D26)
D27: J14.1, U1.73 (PA5/D27)
D28: J14.2, U1.72 (PA6/D28)
D29: J15.1, U1.71 (PA7/D29)
D30: J15.2, U1.60 (PC7/D30)
D31: J16.1, U1.59 (PC6/D31)
D32: J16.2, U1.58 (PC5/D32)
D33: J17.1, U1.57 (PC4/D33)
D34: J17.2, U1.56 (PC3/D34)
D35: J18.1, U1.55 (PC2/D35)
D36: J18.2, U1.54 (PC1/D36)
D37: J19.1, U1.53 (PC0/D37)
D38: J19.2, U1.50 (PD7/D38)
D39: J20.1, U1.70 (PG2/D39)
D40: J20.2, U1.52 (PG1/D40)
D41: J21.1, U1.51 (PG0/D41)
D42: J21.2, U1.42 (PL7/D42)
D43: J22.1, U1.41 (PL6/D43)
D44: J22.2, U1.40 (PL5/~D44)
D45: J23.1, U1.39 (PL4/~D45)
D46: J23.2, U1.38 (PL3/~D46)
D47: J24.1, U1.37 (PL2/D47)
D48: J24.2, U1.36 (PL1/D48)
D49: J25.1, U1.35 (PL0/D49)
D50: J1.1 (MISO), J25.2, U1.22 (PB3/MISO/D50)
D51: J1.4 (MOSI), J26.1, U1.21 (PB2/MOSI/D51)
D52: J1.3 (SCK), J26.2, U1.20 (PB1/SCK/D52)
D53: J27.1, U1.19 (PB0/SS/D53)
FTDI_DTR: C14.2, J39.1
GND: C1.2, C2.2, C3.2, C4.2, C5.2, C6.2, C7.2, C8.2, C9.2, C10.2, C11.1, C12.2, C13.1, D1.1 (K), D2.1 (K), D3.1 (K), D4.3 (common), J1.6 (GND), J27.2, J36.2, J37.2, J39.5, J39.6, R10.2, RJ1.0 (Shield), RJ1.7, RJ1.8, RJ1.9, RJ1.11, SW1.1, SW1.2, U1.11 (GND), U1.32 (GND), U1.62 (GND), U1.81 (GND), U1.99 (GND), U2.5 (GND), U3.1 (GND), U4.8 (GND), U5.5 (GND), Y1.2, Y1.4
unnamed: C13.2, U1.98 (AREF)
unnamed: C15.2, C16.2, R9.2, R10.1, U10.4 (G)
unnamed: D1.2 (A), R3.2
unnamed: D2.2 (A), R6.2
unnamed: D3.2 (A), R7.2
unnamed: D4.1 (A1), F2.1, U7.3 (OUT/IN)
unnamed: D4.2 (A2), F1.2, U6.1 (IN/OUT)
unnamed: R2.2, SW2.3
unnamed: R4.1, RJ1.10
unnamed: R5.1, RJ1.12
unnamed: R8.1, SW2.1
unnamed: U6.3 (OUT/IN), U9.1 (A)
unnamed: U7.1 (IN/OUT), U8.2 (K)
RESET: C14.1, J1.5 (~RST), R1.2, SW1.3 (K), SW1.4 (A), U1.30 (~RESET)
RS485+: RJ1.3, U8.1 (A)
RS485-: RJ1.6, U9.2 (K)
RXD: J39.3, R5.2, RJ1.2, U1.2 (PE0/RXD0/~D0), U2.1 (RO), U5.1 (RO)
TERM_A: F2.2, SW2.2, U2.6 (A), U5.6 (A)
TERM_B: F1.1, R2.1, U2.7 (B), U5.7 (B)
TXD: J39.2, R4.2, RJ1.1, U1.3 (PE1/TXD0/~D1), U2.4 (DI), U5.4 (DI)
XTAL1: C11.2, U1.34 (XTAL1), Y1.1
XTAL2: C12.1, U1.33 (XTAL2), Y1.3

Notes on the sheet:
RS485
Reset
Hotplug Protection
LED Power
Right Green LED
Configuration
Crystal
Standard LEDs
Decoupling
Left Amber LED
RS485 Termination
Extra LEDs
D4 Backlight Enable
12V to 5V
RS485 Power Toggle
Uplink
D13 Aux Light Enable
D13
FTDI Header
ICSP
PLED
